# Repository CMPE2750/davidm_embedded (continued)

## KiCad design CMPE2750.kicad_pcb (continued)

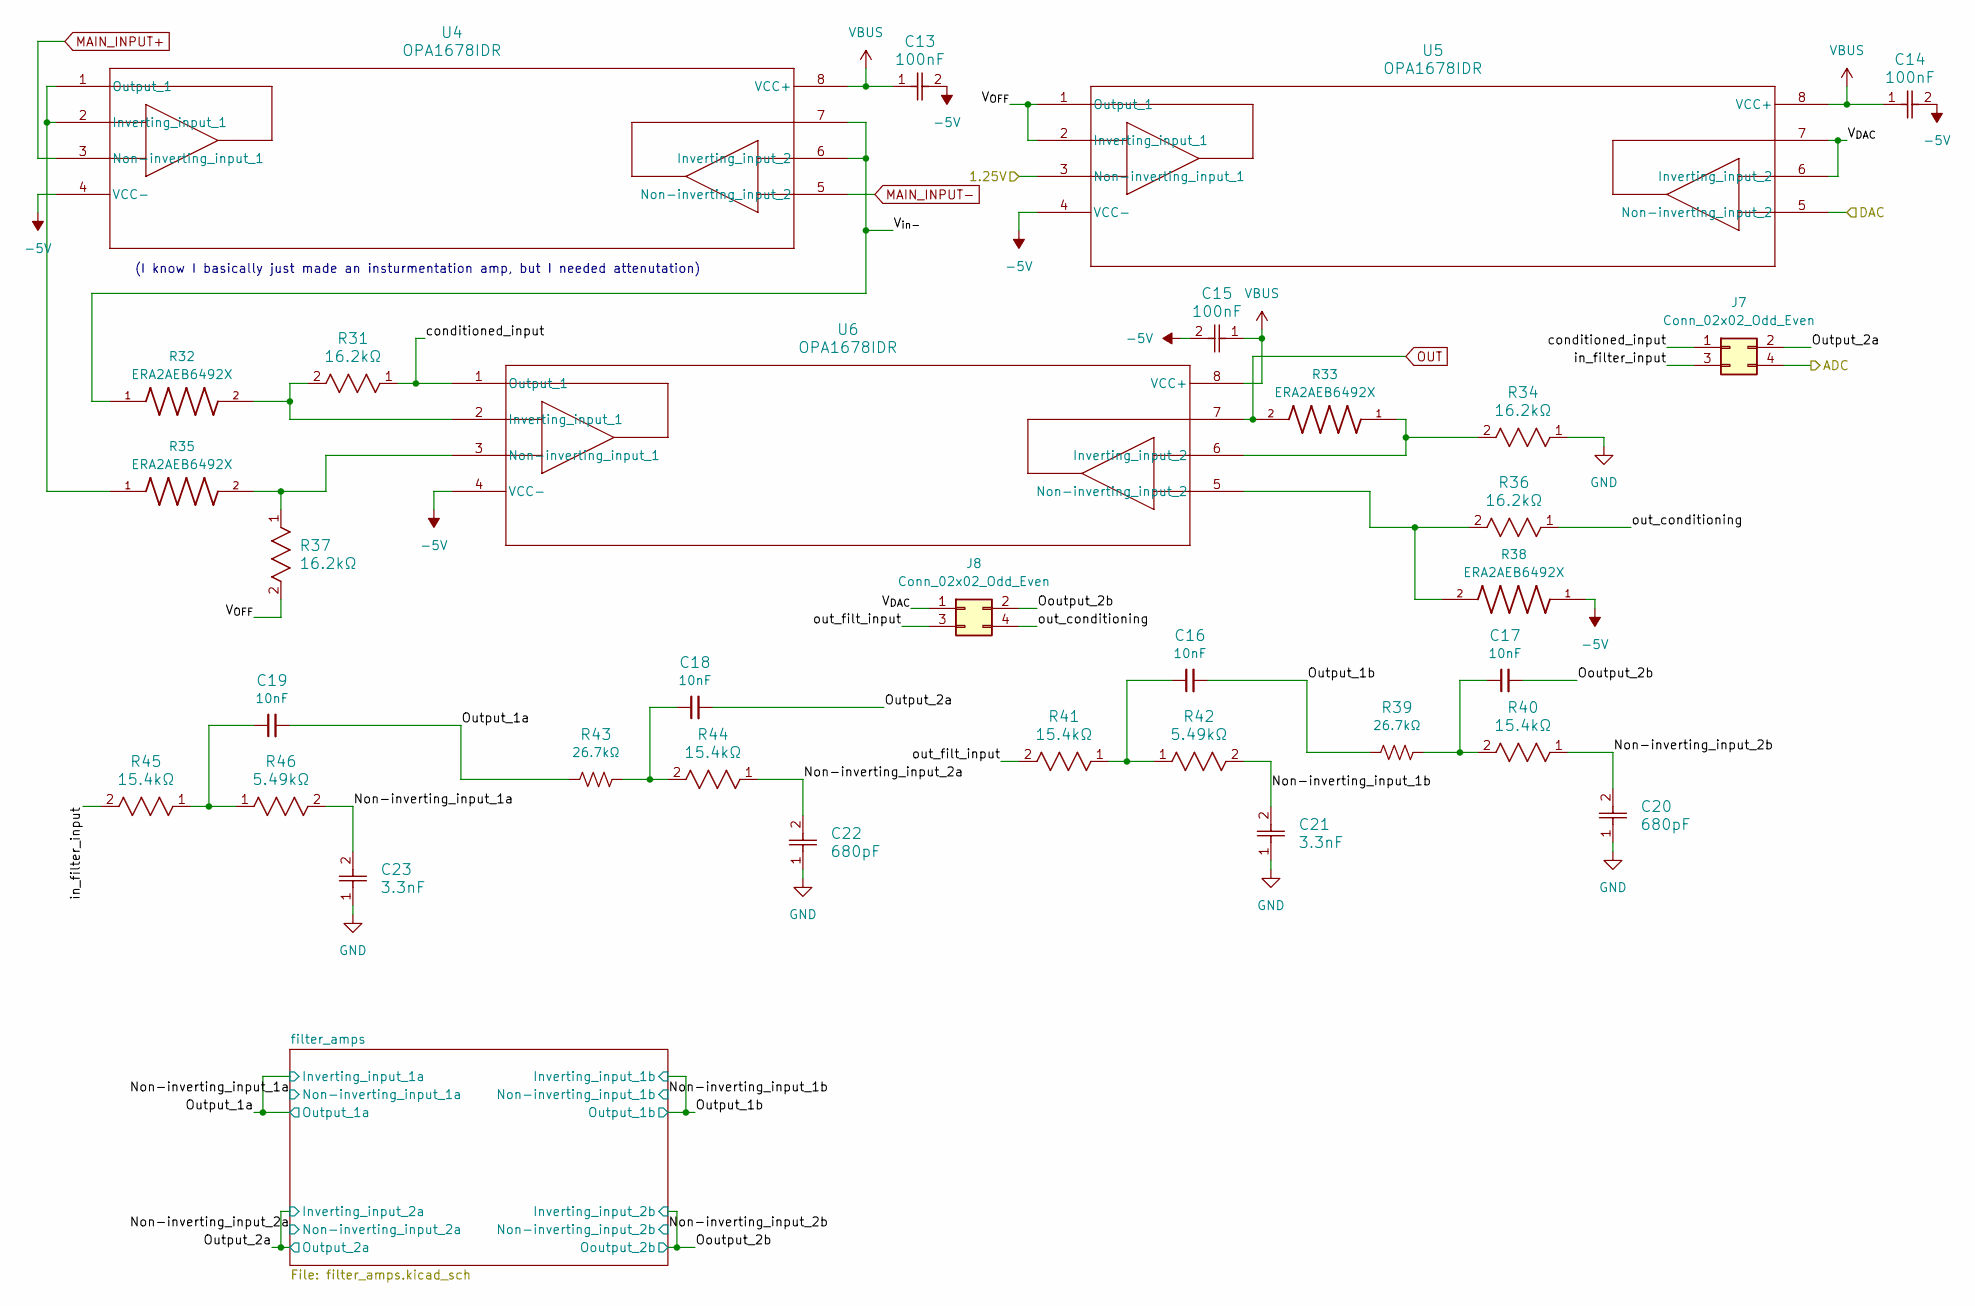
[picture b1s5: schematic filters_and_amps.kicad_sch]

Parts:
C13, C14, C15: 100nF; C_0402_1005Metric
C16, C17, C18, C19: 10nF; C_0805_2012Metric
C20, C22: 680pF; C_0402_1005Metric
C21, C23: 3.3nF; C_0603_1608Metric
J7, J8: Conn_02x02_Odd_Even; PinHeader_2x02_P2.54mm_Vertical
R31, R34, R36, R37: 16.2kΩ; R_0402_1005Metric
R32, R33, R35, R38: ERA2AEB6492X; R_0402_1005Metric; PARTREV 3/1/2020
R39, R43: 26.7kΩ; R_0603_1608Metric
R40, R41, R44, R45: 15.4kΩ; R_0603_1608Metric
R42, R46: 5.49kΩ; R_0402_1005Metric
U4, U5, U6: OPA1678IDR; SOIC-8_3.9x4.9mm_P1.27mm

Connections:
-5V: C13.2, C14.2, C15.2, R38.1, U4.4 (VCC-), U5.4 (VCC-), U6.4 (VCC-); also elsewhere on the board
/1.25V: U5.3 (Non-inverting_input_1); also elsewhere on the board
/ADC: J7.4; also elsewhere on the board
/DAC: U5.5 (Non-inverting_input_2); also elsewhere on the board
/filters and amps/Non-inverting_input_1a: C23.2, R46.2; also elsewhere on the board
/filters and amps/Non-inverting_input_1b: C21.2, R42.2; also elsewhere on the board
/filters and amps/Non-inverting_input_2a: C22.2, R44.1; also elsewhere on the board
/filters and amps/Non-inverting_input_2b: C20.2, R40.1; also elsewhere on the board
/filters and amps/Ooutput_2b: C17.2, J8.2; also elsewhere on the board
/filters and amps/Output_1a: C19.2, R43.1; also elsewhere on the board
/filters and amps/Output_1b: C16.2, R39.1; also elsewhere on the board
/filters and amps/Output_2a: C18.2, J7.2; also elsewhere on the board
/filters and amps/V_{DAC}: J8.1, U5.6 (Inverting_input_2), U5.7
/filters and amps/V_{OFF}: R37.2, U5.1 (Output_1), U5.2 (Inverting_input_1)
/filters and amps/V_{in-}: R32.1, U4.6 (Inverting_input_2), U4.7
/filters and amps/conditioned_input: J7.1, R31.1, U6.1 (Output_1)
/filters and amps/in_filter_input: J7.3, R45.2
/filters and amps/out_conditioning: J8.4, R36.1
/filters and amps/out_filt_input: J8.3, R41.2
GND: C20.1, C21.1, C22.1, C23.1, R34.1; also elsewhere on the board
MAIN_INPUT+: U4.3 (Non-inverting_input_1); also elsewhere on the board
MAIN_INPUT-: U4.5 (Non-inverting_input_2); also elsewhere on the board
unnamed: C16.1, R41.1, R42.1
unnamed: C17.1, R39.2, R40.2
unnamed: C18.1, R43.2, R44.2
unnamed: C19.1, R45.1, R46.1
unnamed: R35.1, U4.1 (Output_1), U4.2 (Inverting_input_1)
unnamed: R31.2, R32.2, U6.2 (Inverting_input_1)
unnamed: R33.1, R34.2, U6.6 (Inverting_input_2)
unnamed: R35.2, R37.1, U6.3 (Non-inverting_input_1)
unnamed: R36.2, R38.2, U6.5 (Non-inverting_input_2)
OUT: R33.2, U6.7; also elsewhere on the board
VBUS: C13.1, C14.1, C15.1, U4.8 (VCC+), U5.8 (VCC+), U6.8 (VCC+); also elsewhere on the board

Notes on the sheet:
(I know I basically just made an insturmentation amp, but I needed attenutation)

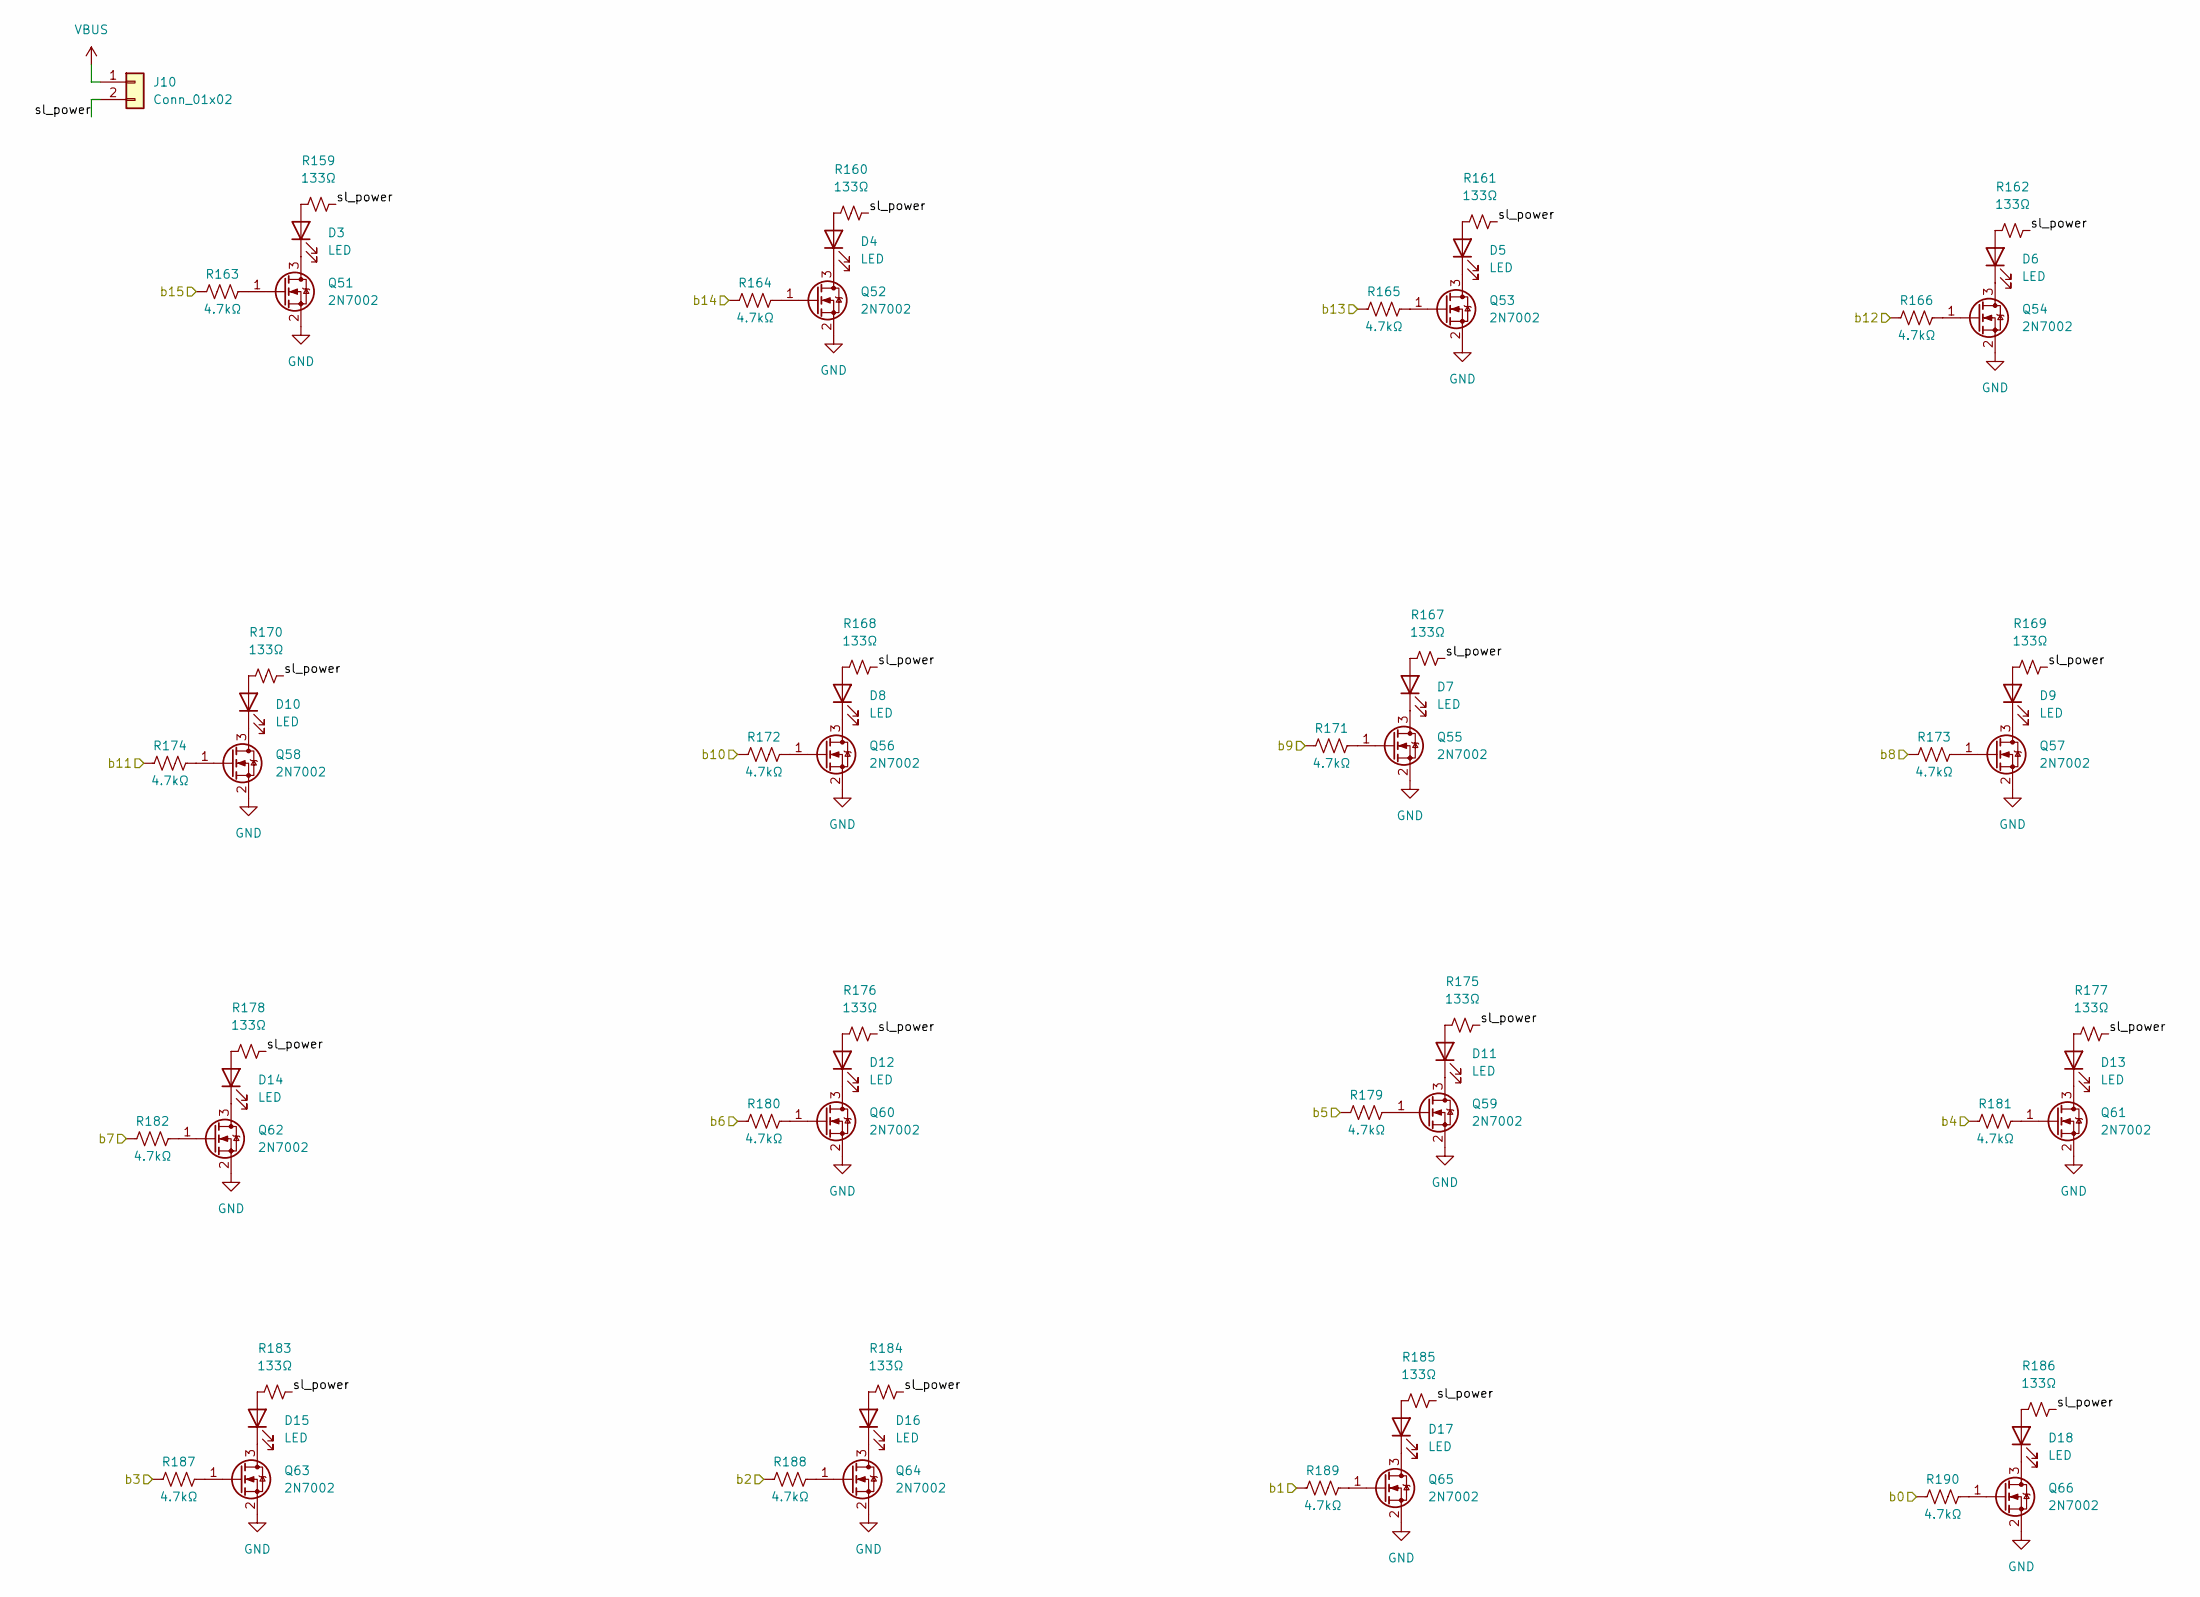
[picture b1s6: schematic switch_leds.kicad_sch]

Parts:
D3, D4, D5, D6, D7, D8, D9, D10, D11, D12, D13, D14, D15, D16, D17, D18: LED; LED_0805_2012Metric
J10: Conn_01x02; PinHeader_1x02_P2.54mm_Vertical
Q51, Q52, Q53, Q54, Q55, Q56, Q57, Q58, Q59, Q60, Q61, Q62, Q63, Q64, Q65, Q66: 2N7002; SOT-23
R159, R160, R161, R162, R167, R168, R169, R170, R175, R176, R177, R178, R183, R184, R185, R186: 133Ω; R_0603_1608Metric
R163, R164, R165, R166, R171, R172, R173, R174, R179, R180, R181, R182, R187, R188, R189, R190: 4.7kΩ; R_0402_1005Metric

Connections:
/b1: R190.1; also elsewhere on the board
/b2: R189.1; also elsewhere on the board
/b3: R188.1; also elsewhere on the board
/b4: R187.1; also elsewhere on the board
/b5: R181.1; also elsewhere on the board
/b6: R179.1; also elsewhere on the board
/b7: R180.1; also elsewhere on the board
/b8: R182.1; also elsewhere on the board
/b9: R173.1; also elsewhere on the board
/b10: R171.1; also elsewhere on the board
/b11: R172.1; also elsewhere on the board
/b12: R174.1; also elsewhere on the board
/b13: R166.1; also elsewhere on the board
/b14: R165.1; also elsewhere on the board
/b15: R164.1; also elsewhere on the board
/b16: R163.1; also elsewhere on the board
/switches/switch_leds/sl_power: J10.2, R159.2, R160.2, R161.2, R162.2, R167.2, R168.2, R169.2, R170.2, R175.2, R176.2, R177.2, R178.2, R183.2, R184.2, R185.2, R186.2
GND: Q51.2 (S), Q52.2 (S), Q53.2 (S), Q54.2 (S), Q55.2 (S), Q56.2 (S), Q57.2 (S), Q58.2 (S), Q59.2 (S), Q60.2 (S), Q61.2 (S), Q62.2 (S), Q63.2 (S), Q64.2 (S), Q65.2 (S), Q66.2 (S); also elsewhere on the board
unnamed: D3.2 (A), R159.1
unnamed: D3.1 (K), Q51.3 (D)
unnamed: D4.2 (A), R160.1
unnamed: D4.1 (K), Q52.3 (D)
unnamed: D5.2 (A), R161.1
unnamed: D5.1 (K), Q53.3 (D)
unnamed: D6.2 (A), R162.1
unnamed: D6.1 (K), Q54.3 (D)
unnamed: D7.2 (A), R167.1
unnamed: D7.1 (K), Q55.3 (D)
unnamed: D8.2 (A), R168.1
unnamed: D8.1 (K), Q56.3 (D)
unnamed: D9.2 (A), R169.1
unnamed: D9.1 (K), Q57.3 (D)
unnamed: D10.2 (A), R170.1
unnamed: D10.1 (K), Q58.3 (D)
unnamed: D11.2 (A), R175.1
unnamed: D11.1 (K), Q59.3 (D)
unnamed: D12.2 (A), R176.1
unnamed: D12.1 (K), Q60.3 (D)
unnamed: D13.2 (A), R177.1
unnamed: D13.1 (K), Q61.3 (D)
unnamed: D14.2 (A), R178.1
unnamed: D14.1 (K), Q62.3 (D)
unnamed: D15.2 (A), R183.1
unnamed: D15.1 (K), Q63.3 (D)
unnamed: D16.2 (A), R184.1
unnamed: D16.1 (K), Q64.3 (D)
unnamed: D17.2 (A), R185.1
unnamed: D17.1 (K), Q65.3 (D)
unnamed: D18.2 (A), R186.1
unnamed: D18.1 (K), Q66.3 (D)
unnamed: Q51.1 (G), R163.2
unnamed: Q52.1 (G), R164.2
unnamed: Q53.1 (G), R165.2
unnamed: Q54.1 (G), R166.2
unnamed: Q55.1 (G), R171.2
unnamed: Q56.1 (G), R172.2
unnamed: Q57.1 (G), R173.2
unnamed: Q58.1 (G), R174.2
unnamed: Q59.1 (G), R179.2
unnamed: Q60.1 (G), R180.2
unnamed: Q61.1 (G), R181.2
unnamed: Q62.1 (G), R182.2
unnamed: Q63.1 (G), R187.2
unnamed: Q64.1 (G), R188.2
unnamed: Q65.1 (G), R189.2
unnamed: Q66.1 (G), R190.2
VBUS: J10.1; also elsewhere on the board

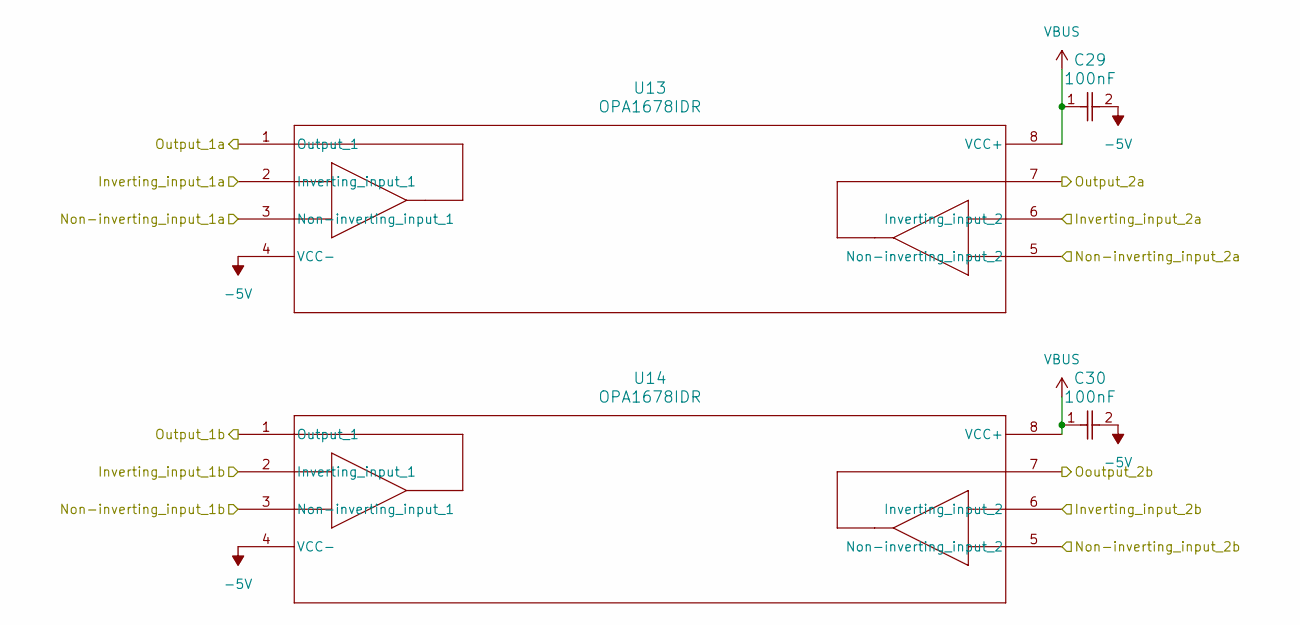
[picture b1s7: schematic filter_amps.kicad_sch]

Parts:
C29, C30: 100nF; C_0402_1005Metric
U13, U14: OPA1678IDR; SOIC-8_3.9x4.9mm_P1.27mm

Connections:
-5V: C29.2, C30.2, U13.4 (VCC-), U14.4 (VCC-); also elsewhere on the board
/filters and amps/Non-inverting_input_1a: U13.3 (Non-inverting_input_1); also elsewhere on the board
/filters and amps/Non-inverting_input_1b: U14.3 (Non-inverting_input_1); also elsewhere on the board
/filters and amps/Non-inverting_input_2a: U13.5 (Non-inverting_input_2); also elsewhere on the board
/filters and amps/Non-inverting_input_2b: U14.5 (Non-inverting_input_2); also elsewhere on the board
/filters and amps/Ooutput_2b: U14.6 (Inverting_input_2), U14.7; also elsewhere on the board
/filters and amps/Output_1a: U13.1 (Output_1), U13.2 (Inverting_input_1); also elsewhere on the board
/filters and amps/Output_1b: U14.1 (Output_1), U14.2 (Inverting_input_1); also elsewhere on the board
/filters and amps/Output_2a: U13.6 (Inverting_input_2), U13.7; also elsewhere on the board
VBUS: C29.1, C30.1, U13.8 (VCC+), U14.8 (VCC+); also elsewhere on the board

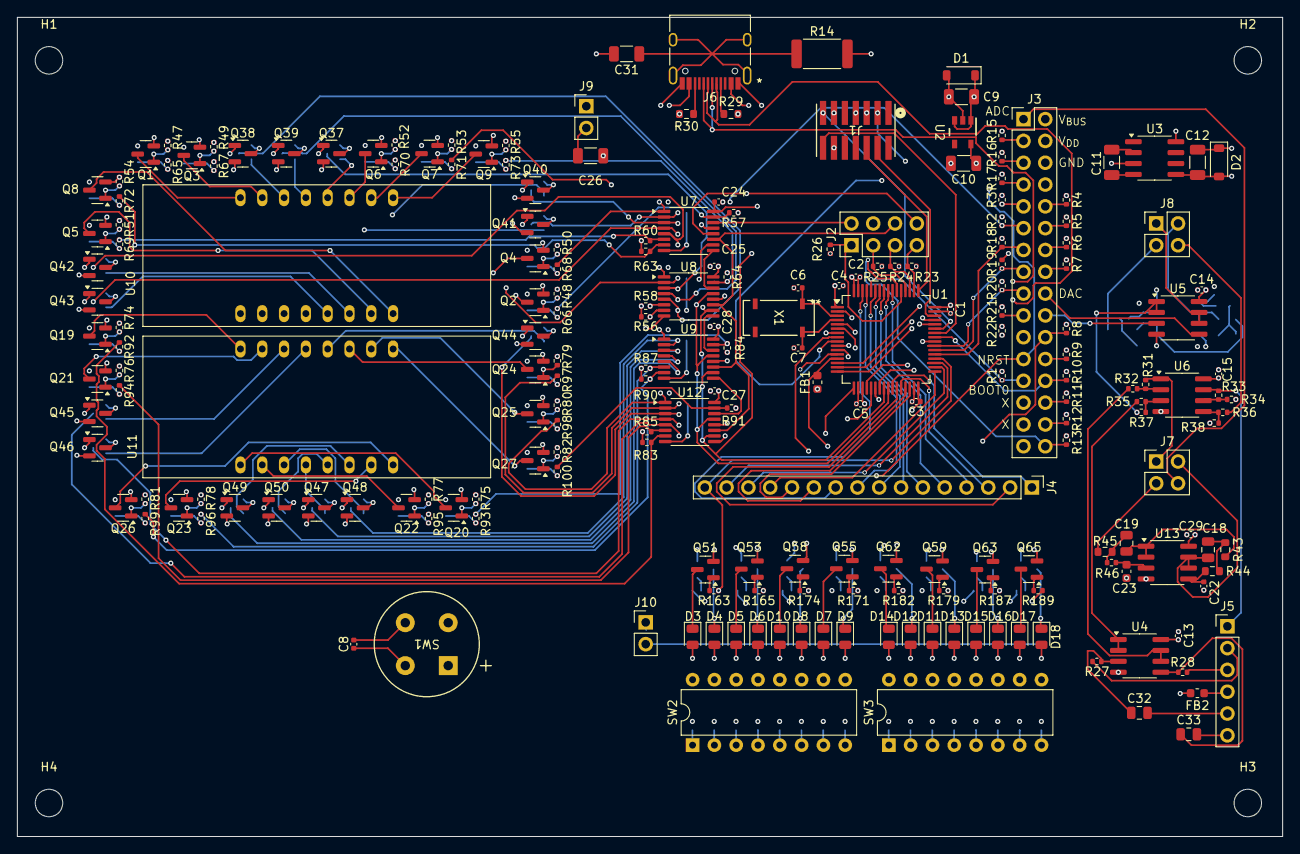
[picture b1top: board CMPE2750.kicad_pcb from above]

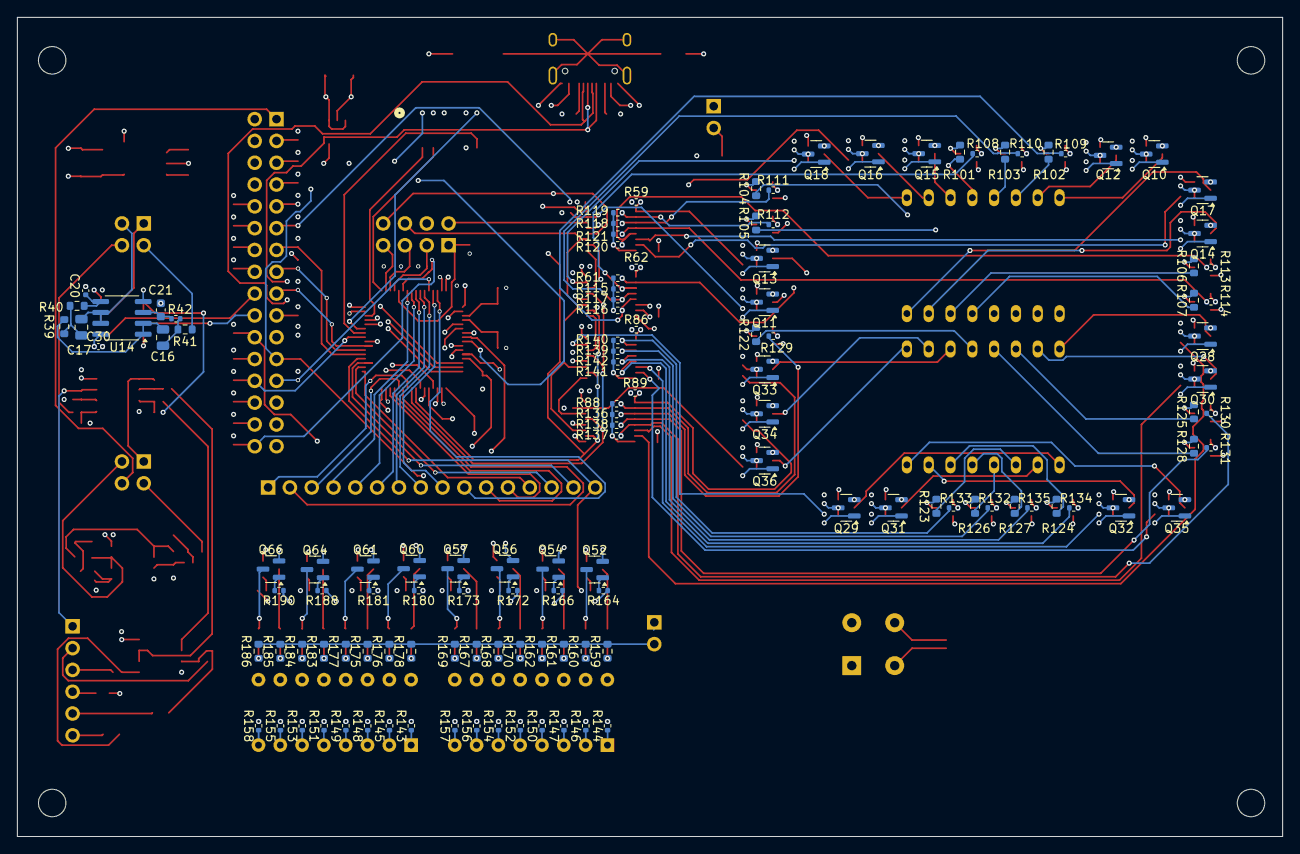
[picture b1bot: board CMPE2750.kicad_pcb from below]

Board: 6 copper layers, 147.4 x 95.4 mm, 341 parts (124 on the bottom side), 282 nets.

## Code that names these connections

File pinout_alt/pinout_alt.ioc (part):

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Mcu.Name=STM32L476R(C-E-G)Tx
Mcu.Package=LQFP64
Mcu.UserName=STM32L476RGTx
PA0.Signal=S_TIM2_CH1
PA10.Mode=Asynchronous
PA10.Signal=USART1_RX
PA11.Mode=Device_Only
PA11.Signal=USB_OTG_FS_DM
PA12.Mode=Device_Only
PA12.Signal=USB_OTG_FS_DP
PA13\ (JTMS-SWDIO).Mode=Serial_Wire
PA13\ (JTMS-SWDIO).Signal=SYS_JTMS-SWDIO
PA14\ (JTCK-SWCLK).Mode=Serial_Wire
PA14\ (JTCK-SWCLK).Signal=SYS_JTCK-SWCLK
PA15\ (JTDI).GPIOParameters=GPIO_Label
PA15\ (JTDI).GPIO_Label=RCLK
PA15\ (JTDI).Signal=GPIO_Output
PA2.Mode=Clock-out-LSCO
PA2.Signal=RCC_LSCO
PA4.Signal=COMP_DAC11_group
PA5.Signal=COMP_DAC12_group
PA8.Mode=Clock-out
PA8.Signal=RCC_MCO
PA9.Mode=Asynchronous
PA9.Signal=USART1_TX
PB0.GPIOParameters=GPIO_PuPd
PB0.GPIO_PuPd=GPIO_PULLDOWN
PB0.Signal=GPIO_Input
PB1.GPIOParameters=GPIO_PuPd
PB1.GPIO_PuPd=GPIO_PULLDOWN
PB1.Signal=GPIO_Input
PB10.GPIOParameters=GPIO_PuPd
PB10.GPIO_PuPd=GPIO_PULLDOWN
PB10.Signal=GPIO_Input
PB11.GPIOParameters=GPIO_PuPd
PB11.GPIO_PuPd=GPIO_PULLDOWN
PB11.Signal=GPIO_Input
PB12.GPIOParameters=GPIO_PuPd
PB12.GPIO_PuPd=GPIO_PULLDOWN
PB12.Signal=GPIO_Input
PB13.GPIOParameters=GPIO_PuPd
PB13.GPIO_PuPd=GPIO_PULLDOWN
PB13.Signal=GPIO_Input
PB14.GPIOParameters=GPIO_PuPd
PB14.GPIO_PuPd=GPIO_PULLDOWN
PB14.Signal=GPIO_Input
PB15.GPIOParameters=GPIO_PuPd
PB15.GPIO_PuPd=GPIO_PULLDOWN
PB15.Signal=GPIO_Input
PB2.GPIOParameters=GPIO_PuPd
PB2.GPIO_PuPd=GPIO_PULLDOWN
PB2.Signal=GPIO_Input
PB3\ (JTDO-TRACESWO).GPIOParameters=GPIO_PuPd
PB3\ (JTDO-TRACESWO).GPIO_PuPd=GPIO_PULLDOWN
PB3\ (JTDO-TRACESWO).Signal=GPIO_Input
PB4\ (NJTRST).GPIOParameters=GPIO_PuPd
PB4\ (NJTRST).GPIO_PuPd=GPIO_PULLDOWN
PB4\ (NJTRST).Signal=GPIO_Input
PB5.GPIOParameters=GPIO_PuPd
PB5.GPIO_PuPd=GPIO_PULLDOWN
PB5.Signal=GPIO_Input
PB6.GPIOParameters=GPIO_PuPd
PB6.GPIO_PuPd=GPIO_PULLDOWN
PB6.Signal=GPIO_Input
PB7.GPIOParameters=GPIO_PuPd
PB7.GPIO_PuPd=GPIO_PULLDOWN
PB7.Signal=GPIO_Input
PB8.GPIOParameters=GPIO_PuPd
PB8.GPIO_PuPd=GPIO_PULLDOWN
PB8.Signal=GPIO_Input
PB9.GPIOParameters=GPIO_PuPd
PB9.GPIO_PuPd=GPIO_PULLDOWN
PB9.Signal=GPIO_Input
PC0.Signal=ADCx_IN1
PC1.Signal=ADCx_IN2
PC10.GPIOParameters=GPIO_Label
PC10.GPIO_Label=SRCLK
PC10.Signal=GPIO_Output
PC11.GPIOParameters=GPIO_Label
PC11.GPIO_Label=SO
PC11.Signal=GPIO_Input
PC12.GPIOParameters=GPIO_Label
PC12.GPIO_Label=SER
PC12.Signal=GPIO_Output
PC14-OSC32_IN\ (PC14).Mode=LSE-External-Oscillator
PC14-OSC32_IN\ (PC14).Signal=RCC_OSC32_IN
PC15-OSC32_OUT\ (PC15).Mode=LSE-External-Oscillator
PC15-OSC32_OUT\ (PC15).Signal=RCC_OSC32_OUT
PC4.GPIOParameters=GPIO_Label
PC4.GPIO_Label=SRCL_N
PC4.Signal=GPIO_Output
PC5.GPIOParameters=GPIO_Label
PC5.GPIO_Label=RCL_N
PC5.Signal=GPIO_Output
PH0-OSC_IN\ (PH0).Signal=GPIO_Input
RCC.HSE_VALUE=8000000
board=custom

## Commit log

2024-11-08 First commit. Preparing to try a change
2024-11-08 Changed how the 14-segment displays were controlled to just use a couple shift registers
2024-11-09 Finished the display and input switch schematics. Also added input buffers to the inputs and made them differential
2024-11-09 Changed some parts so it now only uses one type of op amp
2024-11-11 Almost done. Just going to try and change something
2024-11-11 Schematic is done?
2024-11-12 *Now* it's finished. Maybe.
2024-11-12 Swapped the current limiting diodes for resistors. They *should* be good enough under normal operating conditions. Also added some pull-down resistors. Done?
2024-11-12 Added mounting holes to the schematic, reset the annotations, updated a few footprints, and fixed some issues that were discovered on the ERC.
2024-11-12 Added a ferrite bead and removed a decoupling cap from another ferrite bead
2024-11-17 Component placing partly done. Saving before overwriting the pcb with the templating script output
2024-11-17 Component placing done-ish
2024-11-19 pcb almost done, just need to do the final copper fill
2024-11-21 Made the final fills and the drill files
2024-11-21 finished
2024-11-23 Finished and sent to JLCPCB
2024-11-23 Adding the pinout and the code that's been written so far (not much)
2024-12-06 Commiting changes to the segger project
2024-12-18 Adding the final code version
